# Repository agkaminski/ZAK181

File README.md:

# ZAK181 computer

Work in progress.

## Hardware features

- Z180 CPU,
- 1 MB of static RAM,
- 16 KB bootloader ROM,
- Comact Flash slot in True IDE mode,
- 16 bit GPIO user port,
- 2 UARTs: USB-C and RS232,
- AY-3-8912 sound,
- 80x60 8-color text mode VGA output,
- custom Cherry-MX mechanical keyboard,
- USB-C powered.

## Firmare

ZAKOS code repository is located [here](https://github.com/agkaminski/ZAKOS).

## Memory map

| Start   | End     | Description                              |
|---------|---------|------------------------------------------|
| 0x00000 | 0x03FFF | ROM, disabled after boot, after that RAM |
| 0x04000 | 0xFDFFF | RAM                                      |
| 0xFC000 | 0xFFFFF | Memory mapped I/O, VGA VRAM              |

## I/O map

8-bit I/O is used.

| Start | End  | Description            |
|-------|------|------------------------|
| 0x00  | 0x3F | Z180 internal I/O      |
| 0x40  | 0x5F | VBLANK IRQ acknowledge |
| 0x60  | 0x7F | ROM disable control    |
| 0x80  | 0x9F | Keyboard               |
| 0xA0  | 0xBF | Z80 PIO (user port)    |
| 0xC0  | 0xDF | AY-3-8912              |
| 0xE0  | 0xFF | Compact Flash          |

## Repository structure

### datasheet

Collection of useful datasheets, might be removed in the future.

### keyboard2

Subrepository that contains a hardware project of a mechanical keyboard for the
computer.

### kicad

KiCAD project of the computer's PCB.

### pld

Gateware of PLDs:

- [vga](pld/vga/README.md),
- [ZAK181MD](pld/ZAK181MD/README.md),
- [ZAK181AY](pld/ZAK181AY/README.md).

### schematic.pdf

[Schematic](schematic.pdf) of the computer in a friendly .pdf form.

### 3dprint

3D models designed for FDM 3D priting.

## License

[Attribution-NonCommercial 4.0](LICENSE)

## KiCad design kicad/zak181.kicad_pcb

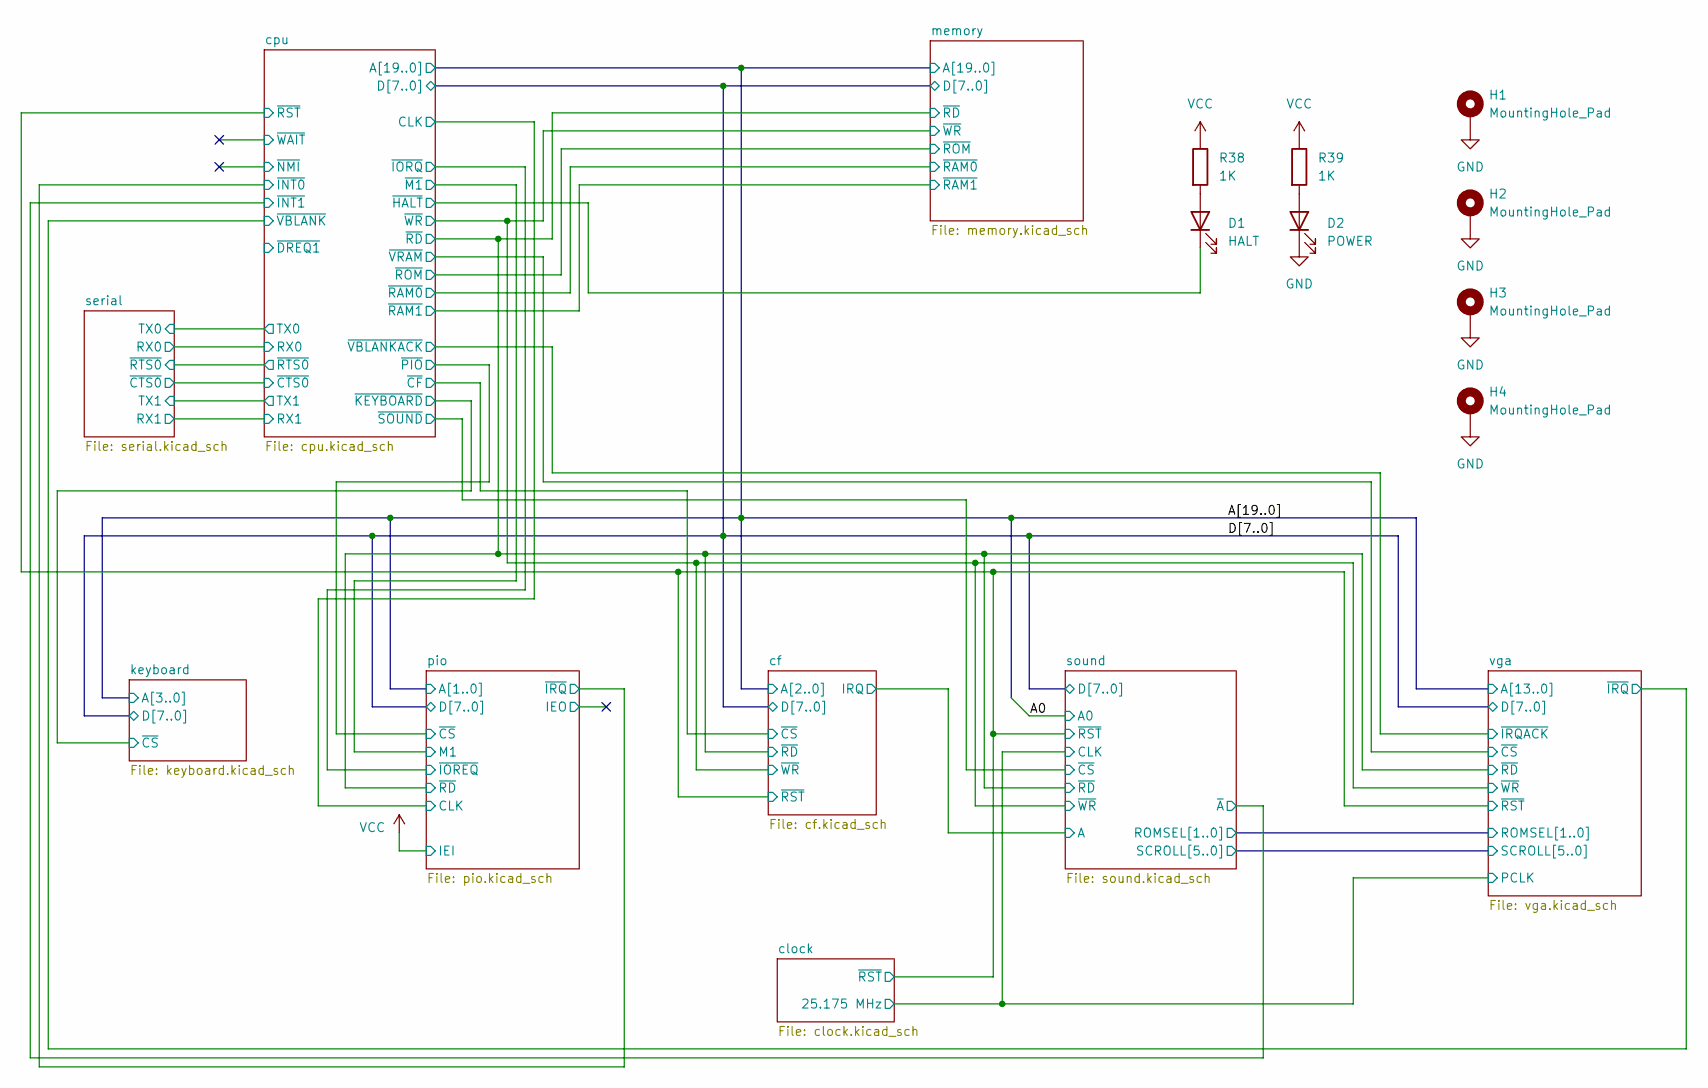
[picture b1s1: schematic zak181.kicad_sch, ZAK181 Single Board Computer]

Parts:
D1: HALT; LED_D5.0mm
D2: POWER; LED_D5.0mm
H1, H2, H3, H4: MountingHole_Pad; MountingHole_3.2mm_M3_Pad_Via
R38, R39: 1K; R_Axial_DIN0207_L6.3mm_D2.5mm_P7.62mm_Horizontal

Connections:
/cpu/~HALT: D1.1 (K); also elsewhere on the board
GND: D2.1 (K), H1.1, H2.1, H3.1, H4.1; also elsewhere on the board
unnamed: D1.2 (A), R38.2
unnamed: D2.2 (A), R39.2
VCC: R38.1, R39.1; also elsewhere on the board

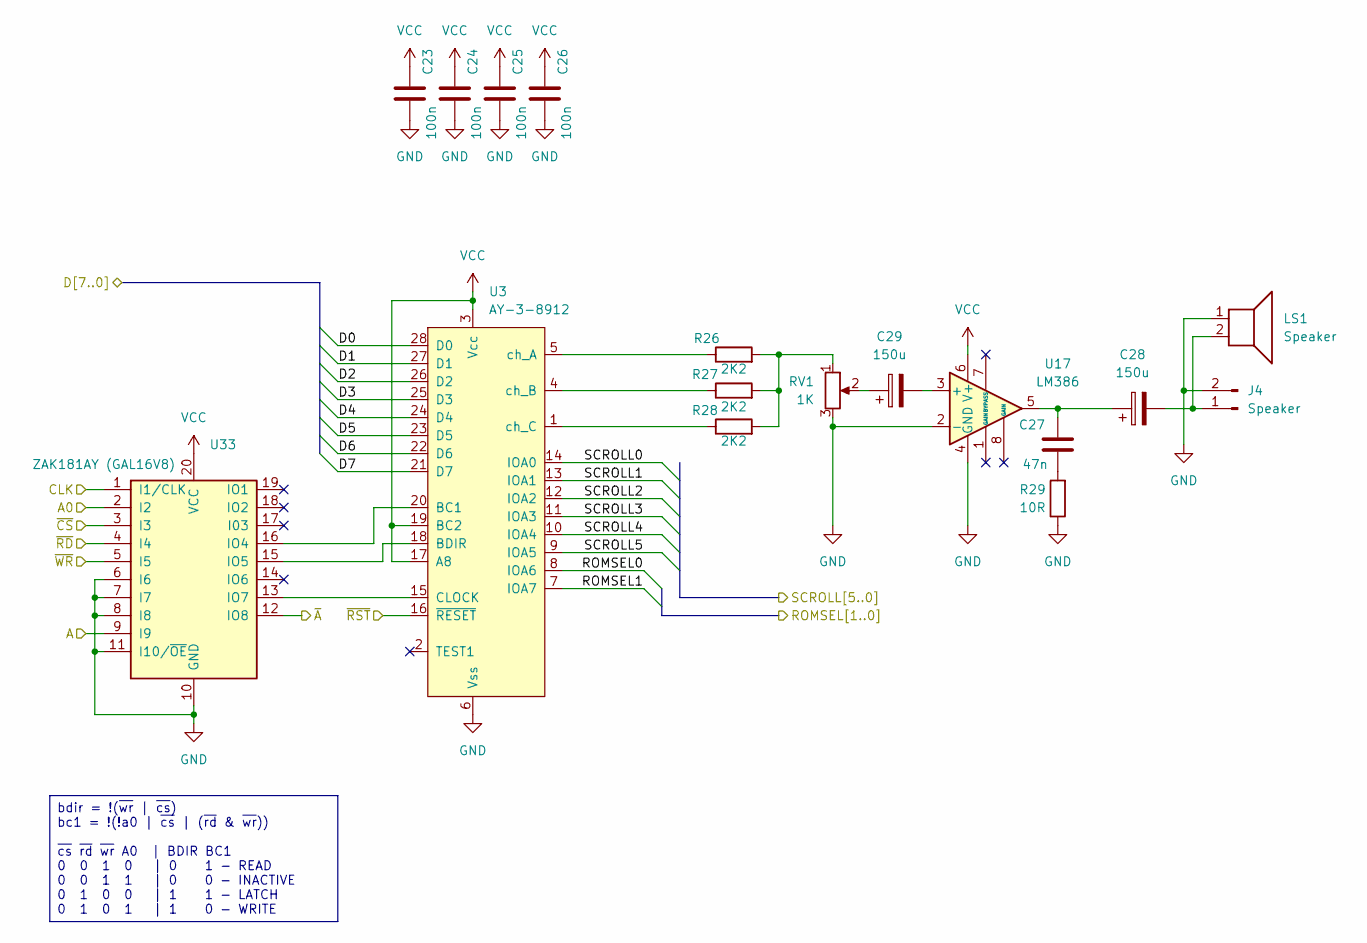
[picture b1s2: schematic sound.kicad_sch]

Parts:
C23, C24, C25, C26: 100n; C_Disc_D5.0mm_W2.5mm_P2.50mm
C27: 47n; C_Disc_D5.0mm_W2.5mm_P2.50mm
C28, C29: 150u; CP_Radial_D6.3mm_P2.50mm
J4: Speaker; PinHeader_1x02_P2.54mm_Vertical
LS1: Speaker; MagneticBuzzer_StarMicronics_QMB-105
R26, R27, R28: 2K2; R_Axial_DIN0207_L6.3mm_D2.5mm_P7.62mm_Horizontal
R29: 10R; R_Axial_DIN0207_L6.3mm_D2.5mm_P7.62mm_Horizontal
RV1: 1K; Potentiometer_Vishay_T73YP_Vertical
U3: AY-3-8912; DIP-28_W15.24mm
U17: LM386; DIP-8_W7.62mm
U33: ZAK181AY (GAL16V8); DIP-20_W7.62mm

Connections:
/A0: U33.2 (I2); also elsewhere on the board
/D0: U3.28 (D0); also elsewhere on the board
/D1: U3.27 (D1); also elsewhere on the board
/D2: U3.26 (D2); also elsewhere on the board
/D3: U3.25 (D3); also elsewhere on the board
/D4: U3.24 (D4); also elsewhere on the board
/D5: U3.23 (D5); also elsewhere on the board
/D6: U3.22 (D6); also elsewhere on the board
/D7: U3.21 (D7); also elsewhere on the board
/cf/IRQ: U33.9 (I9); also elsewhere on the board
/cf/~RD: U33.4 (I4); also elsewhere on the board
/cf/~WR: U33.5 (I5); also elsewhere on the board
/cpu/~INT1: U33.12 (IO8); also elsewhere on the board
/cpu/~RST: U3.16 (~RESET); also elsewhere on the board
/cpu/~SOUND: U33.3 (I3); also elsewhere on the board
/sound/ROMSEL0: U3.8 (IOA6); also elsewhere on the board
/sound/ROMSEL1: U3.7 (IOA7); also elsewhere on the board
/sound/SCROLL0: U3.14 (IOA0); also elsewhere on the board
/sound/SCROLL1: U3.13 (IOA1); also elsewhere on the board
/sound/SCROLL2: U3.12 (IOA2); also elsewhere on the board
/sound/SCROLL3: U3.11 (IOA3); also elsewhere on the board
/sound/SCROLL4: U3.10 (IOA4); also elsewhere on the board
/sound/SCROLL5: U3.9 (IOA5); also elsewhere on the board
/vga/PCLK: U33.1 (I1/CLK); also elsewhere on the board
GND: C23.2, C24.2, C25.2, C26.2, J4.2, LS1.1, R29.1, RV1.3, U3.6 (Vss), U17.2 (-), U17.4 (GND), U33.6 (I6), U33.7 (I7), U33.8 (I8), U33.10 (GND), U33.11 (I10/~OE); also elsewhere on the board
unnamed: C27.1, C28.1, U17.5
unnamed: C27.2, R29.2
unnamed: C29.1, RV1.2
unnamed: C28.2, J4.1, LS1.2
unnamed: R26.2, R27.2, R28.2, RV1.1
unnamed: U3.20 (BC1), U33.16 (IO4)
unnamed: U3.18 (BDIR), U33.15 (IO5)
unnamed: U3.15 (CLOCK), U33.13 (IO7)
unnamed: R26.1, U3.5 (ch_A)
unnamed: R27.1, U3.4 (ch_B)
unnamed: R28.1, U3.1 (ch_C)
unnamed: C29.2, U17.3 (+)
VCC: C23.1, C24.1, C25.1, C26.1, U3.3 (Vcc), U3.17 (A8), U3.19 (BC2), U17.6 (V+), U33.20 (VCC); also elsewhere on the board

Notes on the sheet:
bdir = !(~{wr} | ~{cs}) bc1 = !(!a0 | ~{cs} | (~{rd} & ~{wr})) ~{cs} ~{rd} ~{wr} A0 | BDIR BC1 0 0 1 0 | 0 1 - READ 0 0 1 1 | 0 0 - INACTIVE 0 1 0 0 | 1 1 - LATCH 0 1 0 1 | 1 0 - WRITE

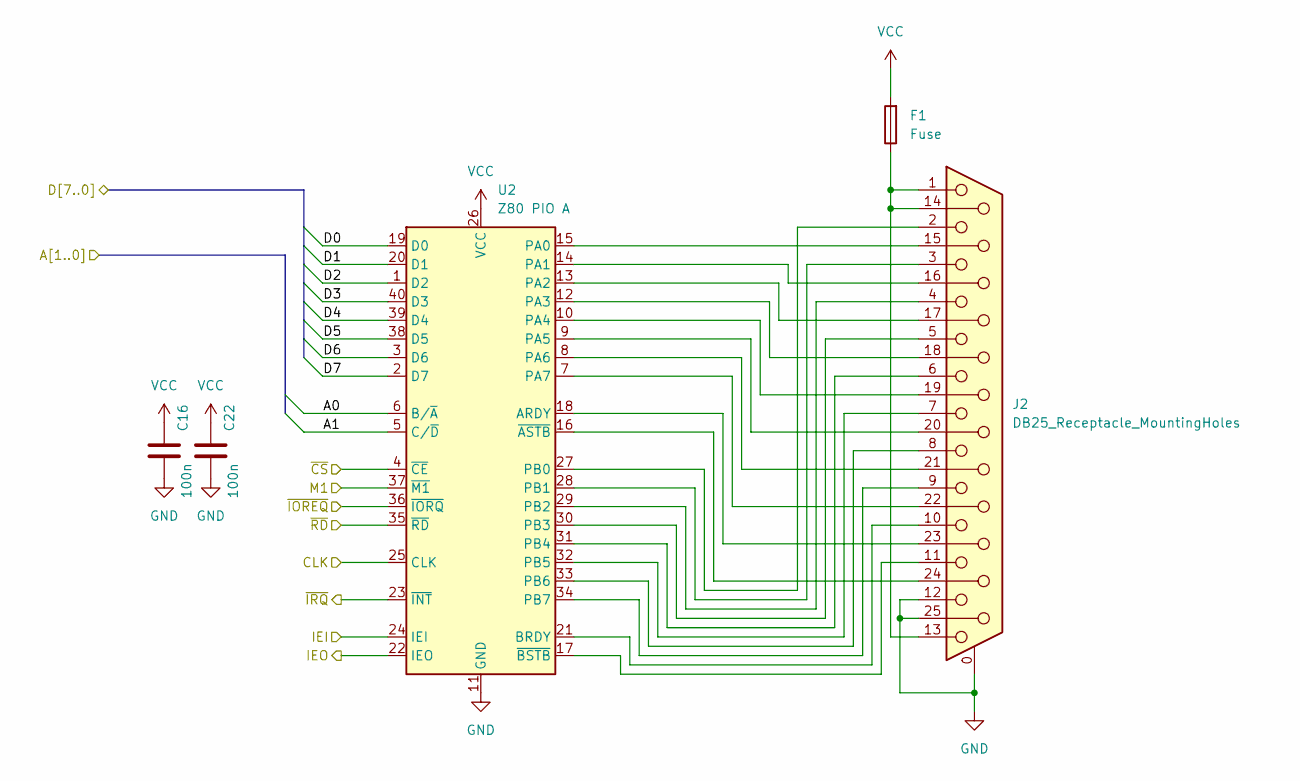
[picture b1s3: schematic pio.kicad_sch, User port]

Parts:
C16, C22: 100n; C_Disc_D5.0mm_W2.5mm_P2.50mm
F1: Fuse; Fuse_Littelfuse_395Series
J2: DB25_Receptacle_MountingHoles; DSUB-25_Socket_Horizontal_P2.77x2.84mm_EdgePinOffset7.70mm_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
U2: Z80 PIO A; DIP-40_W15.24mm

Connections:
/A0: U2.6 (B/~A); also elsewhere on the board
/A1: U2.5 (C/~D); also elsewhere on the board
/D0: U2.19 (D0); also elsewhere on the board
/D1: U2.20 (D1); also elsewhere on the board
/D2: U2.1 (D2); also elsewhere on the board
/D3: U2.40 (D3); also elsewhere on the board
/D4: U2.39 (D4); also elsewhere on the board
/D5: U2.38 (D5); also elsewhere on the board
/D6: U2.3 (D6); also elsewhere on the board
/D7: U2.2 (D7); also elsewhere on the board
/cf/~RD: U2.35 (~RD); also elsewhere on the board
/cpu/CLK: U2.25 (CLK); also elsewhere on the board
/cpu/~INT0: U2.23 (~INT); also elsewhere on the board
/cpu/~IORQ: U2.36 (~IORQ); also elsewhere on the board
/cpu/~M1: U2.37 (~M1); also elsewhere on the board
/cpu/~PIO: U2.4 (~CE); also elsewhere on the board
/pio/IEO: U2.22 (IEO)
GND: C16.2, C22.2, J2.0 (PAD), J2.12, J2.25, U2.11 (GND); also elsewhere on the board
unnamed: F1.1, J2.1, J2.13, J2.14
unnamed: J2.15, U2.15 (PA0)
unnamed: J2.16, U2.14 (PA1)
unnamed: J2.17, U2.13 (PA2)
unnamed: J2.18, U2.12 (PA3)
unnamed: J2.19, U2.10 (PA4)
unnamed: J2.20, U2.9 (PA5)
unnamed: J2.21, U2.8 (PA6)
unnamed: J2.22, U2.7 (PA7)
unnamed: J2.23, U2.18 (ARDY)
unnamed: J2.24, U2.16 (~ASTB)
unnamed: J2.10, U2.21 (BRDY)
unnamed: J2.2, U2.27 (PB0)
unnamed: J2.3, U2.28 (PB1)
unnamed: J2.4, U2.29 (PB2)
unnamed: J2.5, U2.30 (PB3)
unnamed: J2.6, U2.31 (PB4)
unnamed: J2.7, U2.32 (PB5)
unnamed: J2.8, U2.33 (PB6)
unnamed: J2.9, U2.34 (PB7)
unnamed: J2.11, U2.17 (~BSTB)
VCC: C16.1, C22.1, F1.2, U2.24 (IEI), U2.26 (VCC); also elsewhere on the board

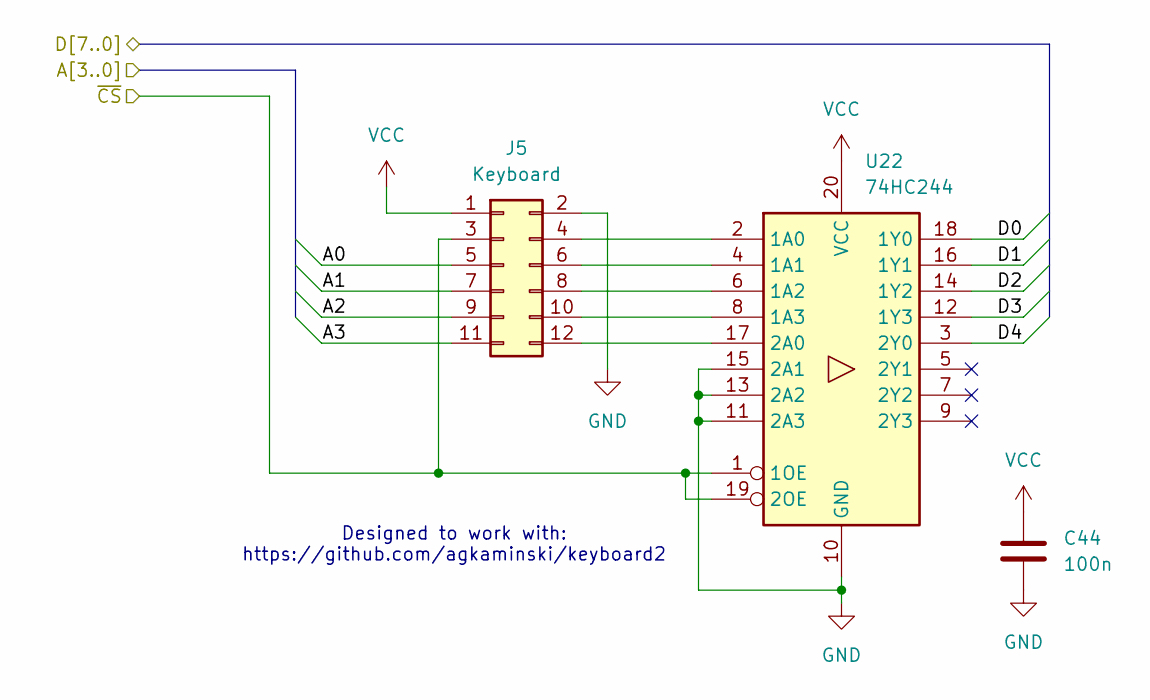
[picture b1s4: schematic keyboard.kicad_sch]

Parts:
C44: 100n; C_Disc_D5.0mm_W2.5mm_P2.50mm
J5: Keyboard; IDC-Header_2x06_P2.54mm_Vertical
U22: 74HC244; DIP-20_W7.62mm

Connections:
/A0: J5.5; also elsewhere on the board
/A1: J5.7; also elsewhere on the board
/A2: J5.9; also elsewhere on the board
/A3: J5.11; also elsewhere on the board
/D0: U22.18 (1Y0); also elsewhere on the board
/D1: U22.16 (1Y1); also elsewhere on the board
/D2: U22.14 (1Y2); also elsewhere on the board
/D3: U22.12 (1Y3); also elsewhere on the board
/D4: U22.3 (2Y0); also elsewhere on the board
/cpu/~KEYBOARD: J5.3, U22.1 (1OE), U22.19 (2OE); also elsewhere on the board
GND: C44.2, J5.2, U22.10 (GND), U22.11 (2A3), U22.13 (2A2), U22.15 (2A1); also elsewhere on the board
unnamed: J5.4, U22.2 (1A0)
unnamed: J5.6, U22.4 (1A1)
unnamed: J5.8, U22.6 (1A2)
unnamed: J5.10, U22.8 (1A3)
unnamed: J5.12, U22.17 (2A0)
VCC: C44.1, J5.1, U22.20 (VCC); also elsewhere on the board

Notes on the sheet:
Designed to work with: https://github.com/agkaminski/keyboard2

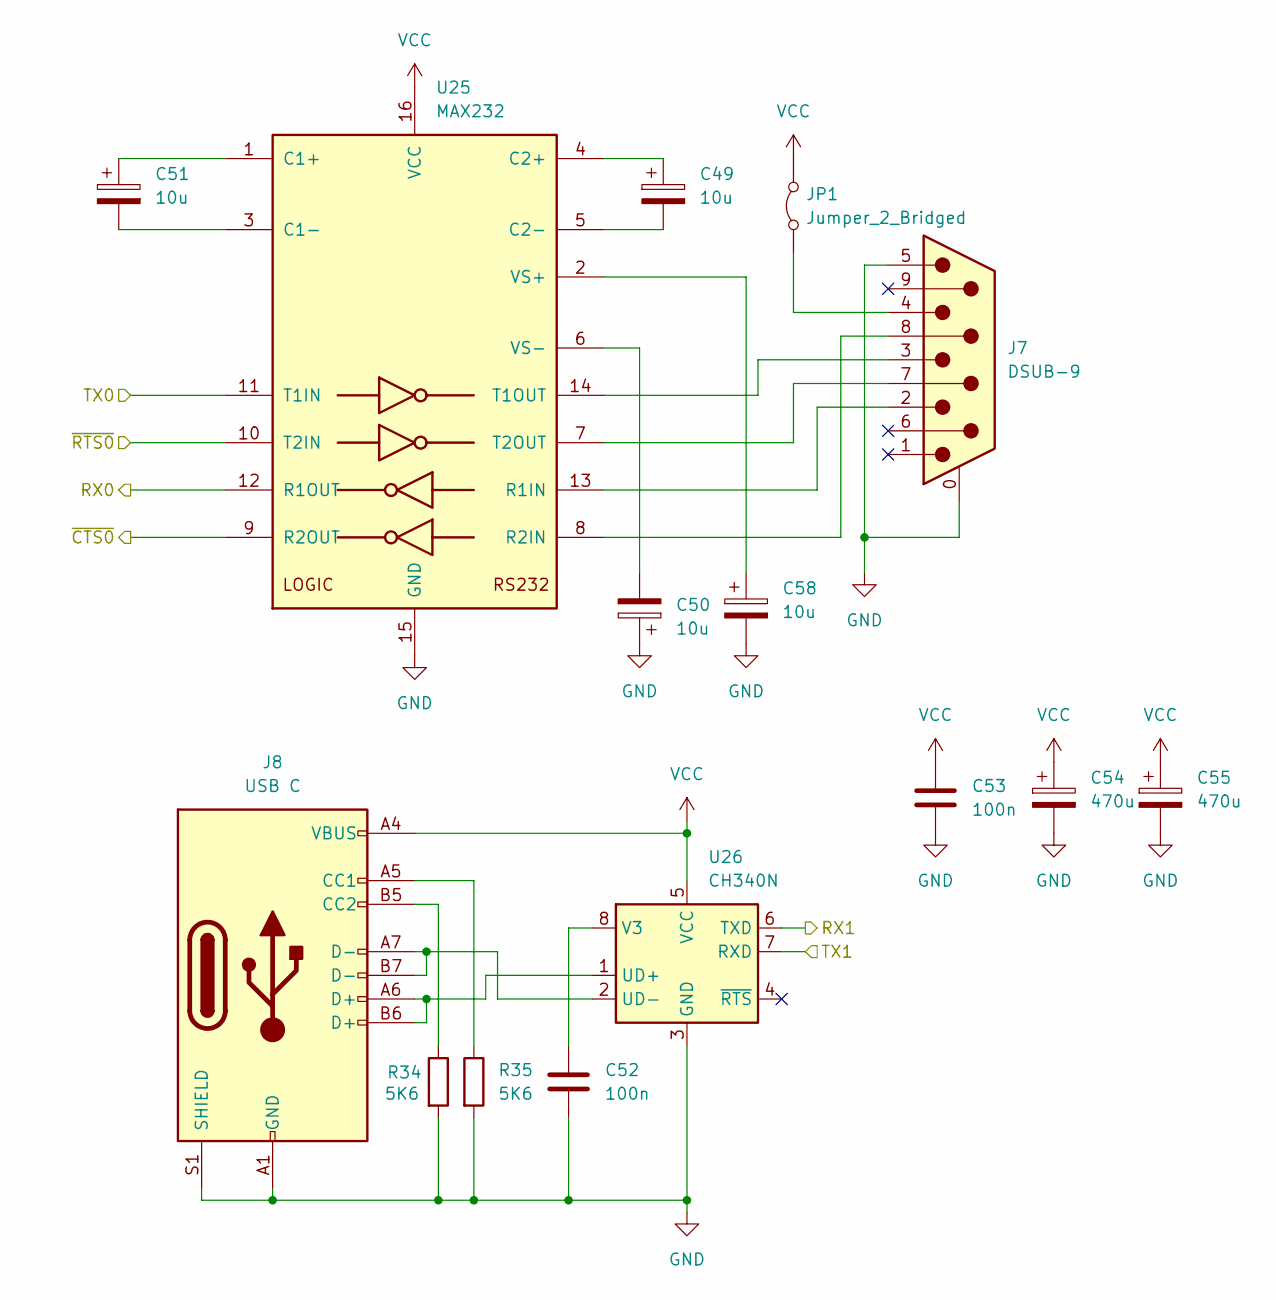
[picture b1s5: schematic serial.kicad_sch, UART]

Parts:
C49, C50, C51, C58: 10u; CP_Radial_D5.0mm_P2.50mm
C52, C53: 100n; C_Disc_D5.0mm_W2.5mm_P2.50mm
C54, C55: 470u; CP_Radial_D10.0mm_P5.00mm
J7: DSUB-9; DSUB-9_Pins_Horizontal_P2.77x2.84mm_EdgePinOffset7.70mm_Hou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
J8: USB C; USB_C_Receptacle_G-Switch_GT-USB-7010ASV
JP1: Jumper_2_Bridged; SolderJumper-2_P1.3mm_Bridged_Pad1.0x1.5mm
R34, R35: 5K6; R_Axial_DIN0207_L6.3mm_D2.5mm_P7.62mm_Horizontal
U25: MAX232; DIP-16_W7.62mm
U26: CH340N; SOP-8_3.9x4.9mm_P1.27mm

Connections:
/cpu/RX0: U25.12 (R1OUT); also elsewhere on the board
/cpu/RX1: U26.6 (TXD); also elsewhere on the board
/cpu/TX0: U25.11 (T1IN); also elsewhere on the board
/cpu/TX1: U26.7 (RXD); also elsewhere on the board
/cpu/~CTS0: U25.9 (R2OUT); also elsewhere on the board
/cpu/~RTS0: U25.10 (T2IN); also elsewhere on the board
GND: C50.1, C52.2, C53.2, C54.2, C55.2, C58.2, J7.0 (PAD), J7.5, J8.A1 (GND), J8.A12 (GND), J8.B1 (GND), J8.B12 (GND), J8.S1 (SHIELD), R34.2, R35.2, U25.15 (GND), U26.3 (GND); also elsewhere on the board
unnamed: J8.A5 (CC1), R35.1
unnamed: J8.B5 (CC2), R34.1
unnamed: J7.4, JP1.1 (A)
unnamed: C51.1, U25.1 (C1+)
unnamed: C51.2, U25.3 (C1-)
unnamed: C49.1, U25.4 (C2+)
unnamed: C49.2, U25.5 (C2-)
unnamed: J7.2, U25.13 (R1IN)
unnamed: J7.8, U25.8 (R2IN)
unnamed: J7.3, U25.14 (T1OUT)
unnamed: J7.7, U25.7 (T2OUT)
unnamed: C58.1, U25.2 (VS+)
unnamed: C50.2, U25.6 (VS-)
unnamed: J8.A6 (D+), J8.B6 (D+), U26.1 (UD+)
unnamed: J8.A7 (D-), J8.B7 (D-), U26.2 (UD-)
unnamed: C52.1, U26.8 (V3)
VCC: C53.1, C54.1, C55.1, J8.A4 (VBUS), J8.A9 (VBUS), J8.B4 (VBUS), J8.B9 (VBUS), JP1.2 (B), U25.16 (VCC), U26.5 (VCC); also elsewhere on the board

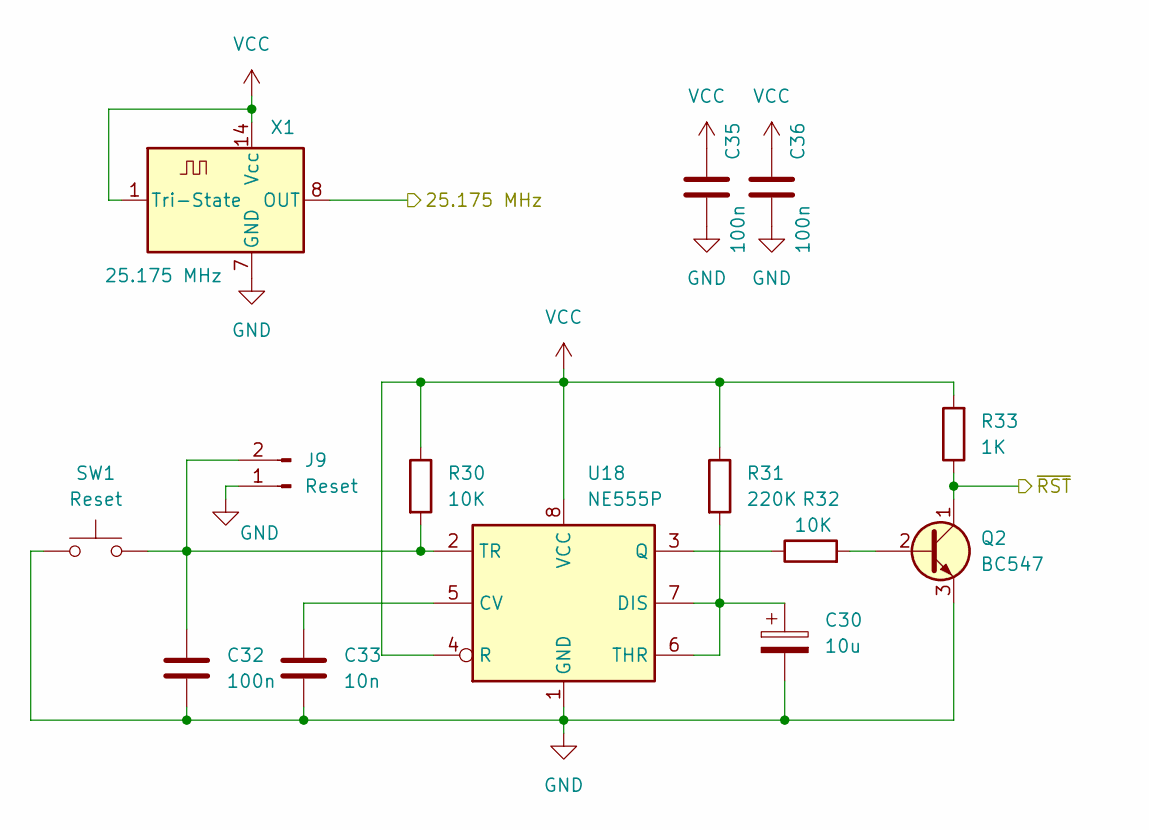
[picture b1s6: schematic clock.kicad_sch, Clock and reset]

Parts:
C30: 10u; CP_Radial_D5.0mm_P2.50mm
C32, C35, C36: 100n; C_Disc_D5.0mm_W2.5mm_P2.50mm
C33: 10n; C_Disc_D5.0mm_W2.5mm_P2.50mm
J9: Reset; PinHeader_1x02_P2.54mm_Vertical
Q2: BC547; TO-92
R30, R32: 10K; R_Axial_DIN0207_L6.3mm_D2.5mm_P7.62mm_Horizontal
R31: 220K; R_Axial_DIN0207_L6.3mm_D2.5mm_P7.62mm_Horizontal
R33: 1K; R_Axial_DIN0207_L6.3mm_D2.5mm_P7.62mm_Horizontal
SW1: Reset; SW_TH_Tactile_Omron_B3F-10xx
U18: NE555P; DIP-8_W7.62mm
X1: 25.175 MHz; Oscillator_DIP-14

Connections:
/cpu/~RST: Q2.1 (C), R33.1; also elsewhere on the board
/vga/PCLK: X1.8 (OUT); also elsewhere on the board
GND: C30.2, C32.2, C33.2, C35.2, C36.2, J9.1, Q2.3 (E), SW1.1, U18.1 (GND), X1.7 (GND); also elsewhere on the board
unnamed: C32.1, J9.2, R30.2, SW1.2, U18.2 (TR)
unnamed: Q2.2 (B), R32.2
unnamed: C33.1, U18.5 (CV)
unnamed: C30.1, R31.2, U18.6 (THR), U18.7 (DIS)
unnamed: R32.1, U18.3 (Q)
VCC: C35.1, C36.1, R30.1, R31.1, R33.2, U18.4 (R), U18.8 (VCC), X1.1 (Tri-State), X1.14 (Vcc); also elsewhere on the board

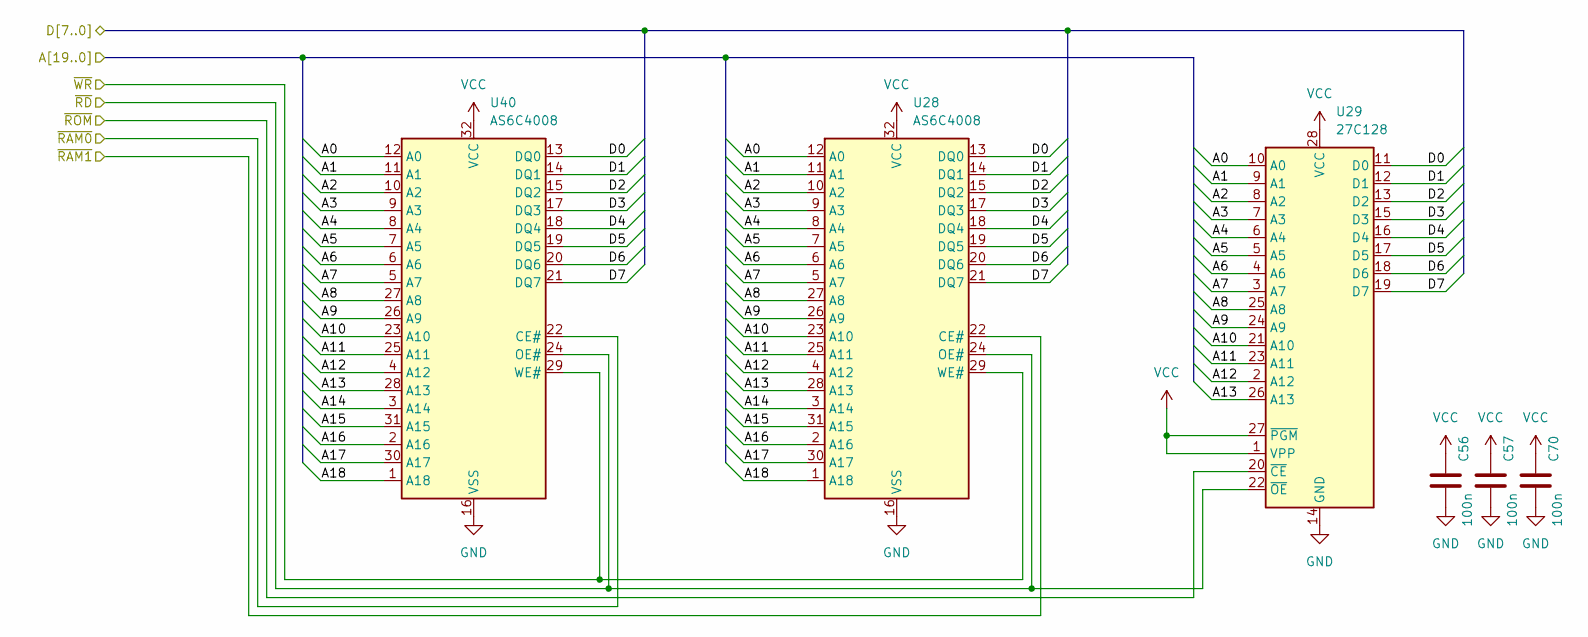
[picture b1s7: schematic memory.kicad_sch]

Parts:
C56, C57, C70: 100n; C_Disc_D5.0mm_W2.5mm_P2.50mm
U28, U40: AS6C4008; DIP-32_W15.24mm
U29: 27C128; DIP-28_W15.24mm

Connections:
/A0: U28.12 (A0), U29.10 (A0), U40.12 (A0); also elsewhere on the board
/A1: U28.11 (A1), U29.9 (A1), U40.11 (A1); also elsewhere on the board
/A2: U28.10 (A2), U29.8 (A2), U40.10 (A2); also elsewhere on the board
/A3: U28.9 (A3), U29.7 (A3), U40.9 (A3); also elsewhere on the board
/A4: U28.8 (A4), U29.6 (A4), U40.8 (A4); also elsewhere on the board
/A5: U28.7 (A5), U29.5 (A5), U40.7 (A5); also elsewhere on the board
/A6: U28.6 (A6), U29.4 (A6), U40.6 (A6); also elsewhere on the board
/A7: U28.5 (A7), U29.3 (A7), U40.5 (A7); also elsewhere on the board
/A8: U28.27 (A8), U29.25 (A8), U40.27 (A8); also elsewhere on the board
/A9: U28.26 (A9), U29.24 (A9), U40.26 (A9); also elsewhere on the board
/A10: U28.23 (A10), U29.21 (A10), U40.23 (A10); also elsewhere on the board
/A11: U28.25 (A11), U29.23 (A11), U40.25 (A11); also elsewhere on the board
/A12: U28.4 (A12), U29.2 (A12), U40.4 (A12); also elsewhere on the board
/A13: U28.28 (A13), U29.26 (A13), U40.28 (A13); also elsewhere on the board
/A14: U28.3 (A14), U40.3 (A14); also elsewhere on the board
/A15: U28.31 (A15), U40.31 (A15); also elsewhere on the board
/A16: U28.2 (A16), U40.2 (A16); also elsewhere on the board
/A17: U28.30 (A17), U40.30 (A17); also elsewhere on the board
/A18: U28.1 (A18), U40.1 (A18); also elsewhere on the board
/D0: U28.13 (DQ0), U29.11 (D0), U40.13 (DQ0); also elsewhere on the board
/D1: U28.14 (DQ1), U29.12 (D1), U40.14 (DQ1); also elsewhere on the board
/D2: U28.15 (DQ2), U29.13 (D2), U40.15 (DQ2); also elsewhere on the board
/D3: U28.17 (DQ3), U29.15 (D3), U40.17 (DQ3); also elsewhere on the board
/D4: U28.18 (DQ4), U29.16 (D4), U40.18 (DQ4); also elsewhere on the board
/D5: U28.19 (DQ5), U29.17 (D5), U40.19 (DQ5); also elsewhere on the board
/D6: U28.20 (DQ6), U29.18 (D6), U40.20 (DQ6); also elsewhere on the board
/D7: U28.21 (DQ7), U29.19 (D7), U40.21 (DQ7); also elsewhere on the board
/cf/~RD: U28.24 (OE#), U29.22 (~OE), U40.24 (OE#); also elsewhere on the board
/cf/~WR: U28.29 (WE#), U40.29 (WE#); also elsewhere on the board
/cpu/~RAM0: U40.22 (CE#); also elsewhere on the board
/cpu/~RAM1: U28.22 (CE#); also elsewhere on the board
/cpu/~ROM: U29.20 (~CE); also elsewhere on the board
GND: C56.2, C57.2, C70.2, U28.16 (VSS), U29.14 (GND), U40.16 (VSS); also elsewhere on the board
VCC: C56.1, C57.1, C70.1, U28.32 (VCC), U29.1 (VPP), U29.27 (~PGM), U29.28 (VCC), U40.32 (VCC); also elsewhere on the board

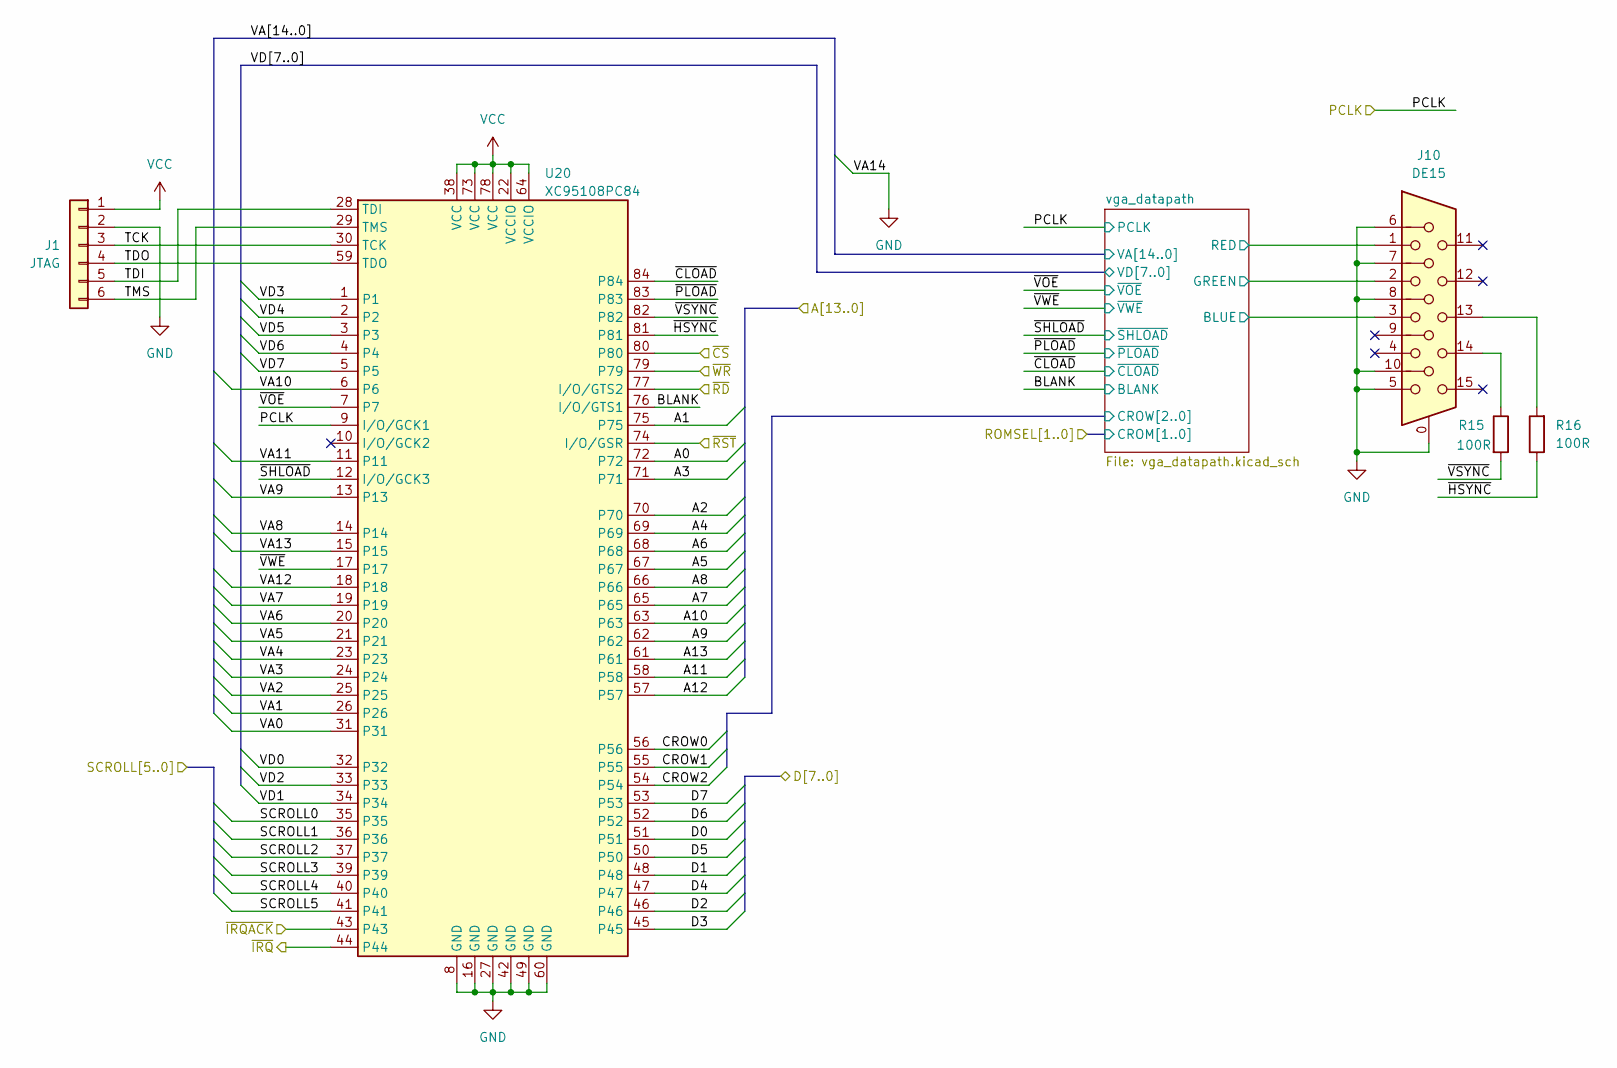
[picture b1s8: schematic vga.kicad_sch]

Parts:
J1: JTAG; PinHeader_1x06_P2.54mm_Vertical
J10: DE15; DSUB-15-HD_Socket_Horizontal_P2.29x1.90mm_EdgePinOffset3.03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
R15, R16: 100R; R_Axial_DIN0207_L6.3mm_D2.5mm_P7.62mm_Horizontal
U20: XC95108PC84; PLCC-84_THT-Socket

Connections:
/A0: U20.72; also elsewhere on the board
/A1: U20.75; also elsewhere on the board
/A2: U20.70; also elsewhere on the board
/A3: U20.71; also elsewhere on the board
/A4: U20.69; also elsewhere on the board
/A5: U20.67; also elsewhere on the board
/A6: U20.68; also elsewhere on the board
/A7: U20.65; also elsewhere on the board
/A8: U20.66; also elsewhere on the board
/A9: U20.62; also elsewhere on the board
/A10: U20.63; also elsewhere on the board
/A11: U20.58; also elsewhere on the board
/A12: U20.57; also elsewhere on the board
/A13: U20.61; also elsewhere on the board
/D0: U20.51; also elsewhere on the board
/D1: U20.48; also elsewhere on the board
/D2: U20.46; also elsewhere on the board
/D3: U20.45; also elsewhere on the board
/D4: U20.47; also elsewhere on the board
/D5: U20.50; also elsewhere on the board
/D6: U20.52; also elsewhere on the board
/D7: U20.53; also elsewhere on the board
/cf/~RD: U20.77 (I/O/GTS2); also elsewhere on the board
/cf/~WR: U20.79; also elsewhere on the board
/cpu/~RST: U20.74 (I/O/GSR); also elsewhere on the board
/cpu/~VBLANKACK: U20.43; also elsewhere on the board
/cpu/~VBLANK: U20.44; also elsewhere on the board
/cpu/~VRAM: U20.80; also elsewhere on the board
/sound/SCROLL0: U20.35; also elsewhere on the board
/sound/SCROLL1: U20.36; also elsewhere on the board
/sound/SCROLL2: U20.37; also elsewhere on the board
/sound/SCROLL3: U20.39; also elsewhere on the board
/sound/SCROLL4: U20.40; also elsewhere on the board
/sound/SCROLL5: U20.41; also elsewhere on the board
/vga/BLANK: U20.76 (I/O/GTS1); also elsewhere on the board
/vga/PCLK: U20.9 (I/O/GCK1); also elsewhere on the board
/vga/TCK: J1.3, U20.30 (TCK)
/vga/TDI: J1.5, U20.28 (TDI)
/vga/TDO: J1.4, U20.59 (TDO)
/vga/TMS: J1.6, U20.29 (TMS)
/vga/VA0: U20.31; also elsewhere on the board
/vga/VA1: U20.26; also elsewhere on the board
/vga/VA2: U20.25; also elsewhere on the board
/vga/VA3: U20.24; also elsewhere on the board
/vga/VA4: U20.23; also elsewhere on the board
/vga/VA5: U20.21; also elsewhere on the board
/vga/VA6: U20.20; also elsewhere on the board
/vga/VA7: U20.19; also elsewhere on the board
/vga/VA8: U20.14; also elsewhere on the board
/vga/VA9: U20.13; also elsewhere on the board
/vga/VA10: U20.6; also elsewhere on the board
/vga/VA11: U20.11; also elsewhere on the board
/vga/VA12: U20.18; also elsewhere on the board
/vga/VA13: U20.15; also elsewhere on the board
/vga/VD0: U20.32; also elsewhere on the board
/vga/VD1: U20.34; also elsewhere on the board
/vga/VD2: U20.33; also elsewhere on the board
/vga/VD3: U20.1; also elsewhere on the board
/vga/VD4: U20.2; also elsewhere on the board
/vga/VD5: U20.3; also elsewhere on the board
/vga/VD6: U20.4; also elsewhere on the board
/vga/VD7: U20.5; also elsewhere on the board
/vga/vga_datapath/BLUE: J10.3; also elsewhere on the board
/vga/vga_datapath/CROW0: U20.56; also elsewhere on the board
/vga/vga_datapath/CROW1: U20.55; also elsewhere on the board
/vga/vga_datapath/CROW2: U20.54; also elsewhere on the board
/vga/vga_datapath/GREEN: J10.2; also elsewhere on the board
/vga/vga_datapath/RED: J10.1; also elsewhere on the board
/vga/~CLOAD: U20.84; also elsewhere on the board
/vga/~HSYNC: R16.1, U20.81
/vga/~PLOAD: U20.83; also elsewhere on the board
/vga/~SHLOAD: U20.12 (I/O/GCK3); also elsewhere on the board
/vga/~VOE: U20.7; also elsewhere on the board
/vga/~VSYNC: R15.2, U20.82
/vga/~VWE: U20.17; also elsewhere on the board
GND: J1.2, J10.0, J10.5, J10.6, J10.7, J10.8, J10.10, U20.8 (GND), U20.16 (GND), U20.27 (GND), U20.42 (GND), U20.49 (GND), U20.60 (GND); also elsewhere on the board
unnamed: J10.13, R16.2
unnamed: J10.14, R15.1
VCC: J1.1, U20.22 (VCCIO), U20.38 (VCC), U20.64 (VCCIO), U20.73 (VCC), U20.78 (VCC); also elsewhere on the board

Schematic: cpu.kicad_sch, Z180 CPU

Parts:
C38, C39: 22p; C_Disc_D5.0mm_W2.5mm_P2.50mm
C40, C41, C42, C72: 100n; C_Disc_D5.0mm_W2.5mm_P2.50mm
IC1: Z180; PLCC-68_THT-Socket; Manufacturer_Part_Number Z8S18033VSG; Mouser Part Number 692-Z8S18033VSG
RN2: 47K; R_Array_SIP9
U8: 74HC138; DIP-16_W7.62mm
U31: ZAK181MD (GAL16V8); DIP-20_W7.62mm
Y2: 12.288 MHz; Crystal_HC49-4H_Vertical

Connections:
/A0: IC1.14 (A0); also elsewhere on the board
/A1: IC1.15 (A1); also elsewhere on the board
/A2: IC1.16 (A2); also elsewhere on the board
/A3: IC1.17 (A3); also elsewhere on the board
/A4: IC1.19 (A4); also elsewhere on the board
/A5: IC1.20 (A5), U8.3 (A2); also elsewhere on the board
/A6: IC1.21 (A6), U8.2 (A1); also elsewhere on the board
/A7: IC1.22 (A7), U8.1 (A0); also elsewhere on the board
/A8: IC1.23 (A8); also elsewhere on the board
/A9: IC1.24 (A9); also elsewhere on the board
/A10: IC1.25 (A10); also elsewhere on the board
/A11: IC1.26 (A11); also elsewhere on the board
/A12: IC1.27 (A12); also elsewhere on the board
/A13: IC1.28 (A13), U31.8 (I8); also elsewhere on the board
/A14: IC1.29 (A14), U31.7 (I7); also elsewhere on the board
/A15: IC1.30 (A15), U31.6 (I6); also elsewhere on the board
/A16: IC1.31 (A16), U31.5 (I5); also elsewhere on the board
/A17: IC1.32 (A17), U31.4 (I4); also elsewhere on the board
/A18: IC1.33 (A18/TOUT), U31.3 (I3); also elsewhere on the board
/A19: IC1.35 (A19), U31.2 (I2)
/D0: IC1.37 (D0), U31.11 (I10/~OE); also elsewhere on the board
/D1: IC1.38 (D1); also elsewhere on the board
/D2: IC1.39 (D2); also elsewhere on the board
/D3: IC1.40 (D3); also elsewhere on the board
/D4: IC1.41 (D4); also elsewhere on the board
/D5: IC1.42 (D5); also elsewhere on the board
/D6: IC1.43 (D6); also elsewhere on the board
/D7: IC1.44 (D7); also elsewhere on the board
/cf/~CS: U8.7 (~Y7); also elsewhere on the board
/cf/~RD: IC1.67 (~RD); also elsewhere on the board
/cf/~WR: IC1.66 (~WR); also elsewhere on the board
/cpu/CLK: IC1.68 (PHI); also elsewhere on the board
/cpu/RX0: IC1.49 (RXA0); also elsewhere on the board
/cpu/RX1: IC1.53 (RXA1); also elsewhere on the board
/cpu/TX0: IC1.48 (TXA0); also elsewhere on the board
/cpu/TX1: IC1.51 (TXA1); also elsewhere on the board
/cpu/~CTS0: IC1.46 (~CTS0); also elsewhere on the board
/cpu/~DREQ1: IC1.58 (~DREQ1), RN2.2 (R1)
/cpu/~HALT: IC1.60 (~HALT); also elsewhere on the board
/cpu/~INT0: IC1.10 (~INT0), RN2.8 (R7); also elsewhere on the board
/cpu/~INT1: IC1.11 (~INT1), RN2.7 (R6); also elsewhere on the board
/cpu/~IORQ: IC1.62 (~IORQ), U8.4 (~E0); also elsewhere on the board
/cpu/~KEYBOARD: U8.11 (~Y4); also elsewhere on the board
/cpu/~M1: IC1.65 (~M1), U8.6 (E2); also elsewhere on the board
/cpu/~MREQ: IC1.63 (~MREQ), U31.9 (I9)
/cpu/~NMI: IC1.9 (~NMI), RN2.9 (R8)
/cpu/~PIO: U8.10 (~Y5); also elsewhere on the board
/cpu/~RAM0: U31.12 (IO8); also elsewhere on the board
/cpu/~RAM1: U31.19 (IO1); also elsewhere on the board
/cpu/~ROMDIS: U8.12 (~Y3), U31.14 (IO6)
/cpu/~ROM: U31.13 (IO7); also elsewhere on the board
/cpu/~RST: IC1.8 (~RESET), U31.16 (IO4); also elsewhere on the board
/cpu/~RTS0: IC1.45 (~RTS0); also elsewhere on the board
/cpu/~SOUND: U8.9 (~Y6); also elsewhere on the board
/cpu/~VBLANKACK: U8.13 (~Y2); also elsewhere on the board
/cpu/~VBLANK: IC1.12 (~INT2), RN2.6 (R5); also elsewhere on the board
/cpu/~VRAM: U31.18 (IO2); also elsewhere on the board
/cpu/~WAIT: IC1.5 (~WAIT), RN2.5 (R4)
GND: C38.1, C39.1, C40.2, C41.2, C42.2, C72.2, IC1.1 (VSS_1), IC1.2 (VSS_2), IC1.18 (VSS_3), IC1.36 (VSS_4), U8.5 (~E1), U8.8 (GND), U31.1 (I1/CLK), U31.10 (GND); also elsewhere on the board
unnamed: IC1.50 (CKA0/~DREQ0), RN2.3 (R2)
unnamed: C39.2, IC1.4 (EXTAL), Y2.2
unnamed: C38.2, IC1.3 (XTAL), Y2.1
unnamed: IC1.7 (~BUSREQ), RN2.4 (R3)
VCC: C40.1, C41.1, C42.1, C72.1, IC1.34 (VDD), RN2.1 (common), U8.16 (VCC), U31.20 (VCC); also elsewhere on the board

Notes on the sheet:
Z180 internal I/O (0x00:0x3F)
GAL16V8 ZAK181MD NC A19 A18 A17 A16 A15 A14 A13 /MREQ GND DAT /RAM0 /ROM /ROMCTRL NC /RST ROMDIS /VRAM /RAM1 VCC VRAM = A14 * A15 * A16 * A17 * A18 * A19 * MREQ ROM = /A14 * /A15 * /A16 * /A17 * /A18 * /A19 * MREQ * /ROMDIS RAM0 = /VRAM * /ROM * MREQ * /A19 RAM1 = /VRAM * /ROM * MREQ * A19 ROMDIS =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
